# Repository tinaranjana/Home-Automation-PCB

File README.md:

# Home Automation PCB

A 4-layer smart home PCB designed in KiCad, built around the ESP32-WROOM-32. It controls 3 appliances (Light, AC and Exhaust) through opto-isolated relay channels.

## Features
- ESP32-WROOM-32 main controller
- 3 relay channels with PC817 optocoupler isolation
- NPN transistor driver and 1N4007 flyback diode on each channel
- LDR and DHT11 sensor headers, I2C LCD header
- 4 push-button inputs and a UART header
- 12 V DC input with 5 V (L7805) and 3.3 V (AMS1117) regulation

## Design Details
- Tool: KiCad 10
- 4 copper layers: F.Cu, In1.Cu, In2.Cu, B.Cu
- 209 pads, 67 nets, 44 vias, 0 unrouted
- Antenna keep-out zone for the ESP32

## Files
- `Home_Automation_PCB.pdf`: schematic, PCB layers, 3D views and BOM
- `ibom.html`: interactive BOM

## Status
Learning project. Feedback and suggestions are welcome!

## Author
Ranjana Yadav
linkedin.com/in/ranjana-yadav-ece

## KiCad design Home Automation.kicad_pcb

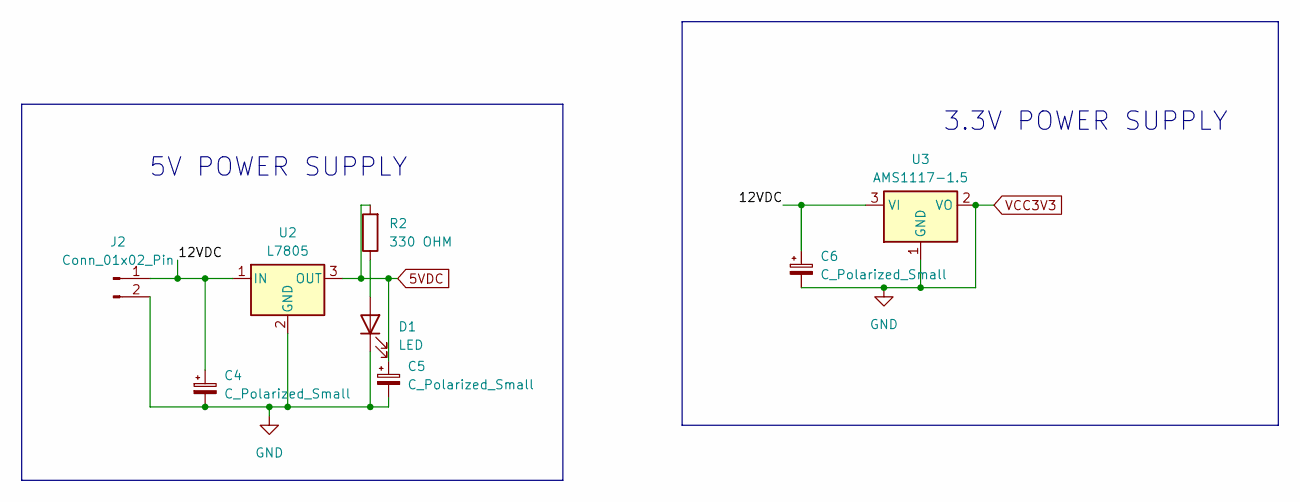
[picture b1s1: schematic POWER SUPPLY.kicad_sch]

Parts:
C4, C5, C6: C_Polarized_Small; CP_Elec_8x6.2
D1: LED; LED_D1.8mm_W3.3mm_H2.4mm
J2: Conn_01x02_Pin; TerminalBlock_Phoenix_MKDS-1,5-2_1x02_P5.00mm_Horizontal
R2: 330 OHM; R_0603_1608Metric
U2: L7805; TO-252-2
U3: AMS1117-1.5; SOT-223-3_TabPin2

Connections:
5VDC: C5.1, R2.2, U2.3 (OUT); also elsewhere on the board
/POWER SUPPLY/12VDC: C4.1, C6.1, J2.1, U2.1 (IN), U3.3 (VI)
GND: C4.2, C5.2, C6.2, D1.1 (K), J2.2, U2.2 (GND), U3.1 (GND), U3.2 (VO); also elsewhere on the board
unnamed: D1.2 (A), R2.1

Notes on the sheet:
5V POWER SUPPLY
3.3V POWER SUPPLY

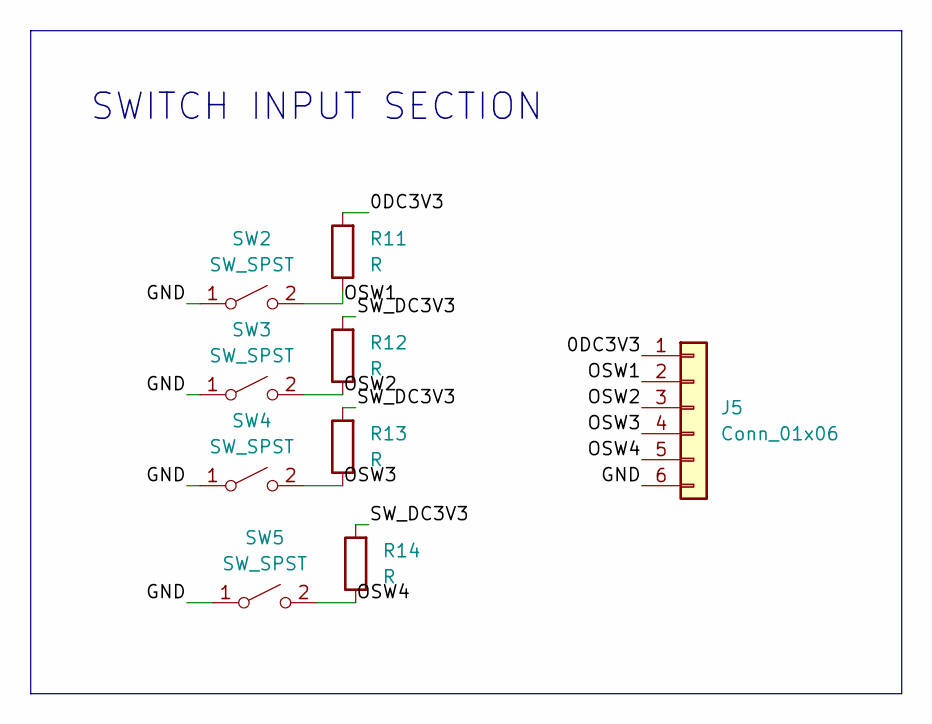
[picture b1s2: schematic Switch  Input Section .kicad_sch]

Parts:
J5: Conn_01x06; PinHeader_1x06_P2.54mm_Vertical_SMD_Pin1Left
R11, R12, R13, R14: R; R_0603_1608Metric
SW2, SW3, SW4, SW5: SW_SPST; SW_PUSH_6mm

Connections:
/Switch Input Section/0DC3V3: J5.1, R11.2
/Switch Input Section/GND: J5.6, SW2.1 (A), SW3.1 (A), SW4.1 (A), SW5.1 (A)
/Switch Input Section/OSW1: J5.2, R11.1, SW2.2 (B)
/Switch Input Section/OSW2: J5.3, R12.1, SW3.2 (B)
/Switch Input Section/OSW3: J5.4, R13.1, SW4.2 (B)
/Switch Input Section/OSW4: J5.5, R14.1, SW5.2 (B)
/Switch Input Section/SW_DC3V3: R12.2, R13.2, R14.2

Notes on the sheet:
SWITCH INPUT SECTION

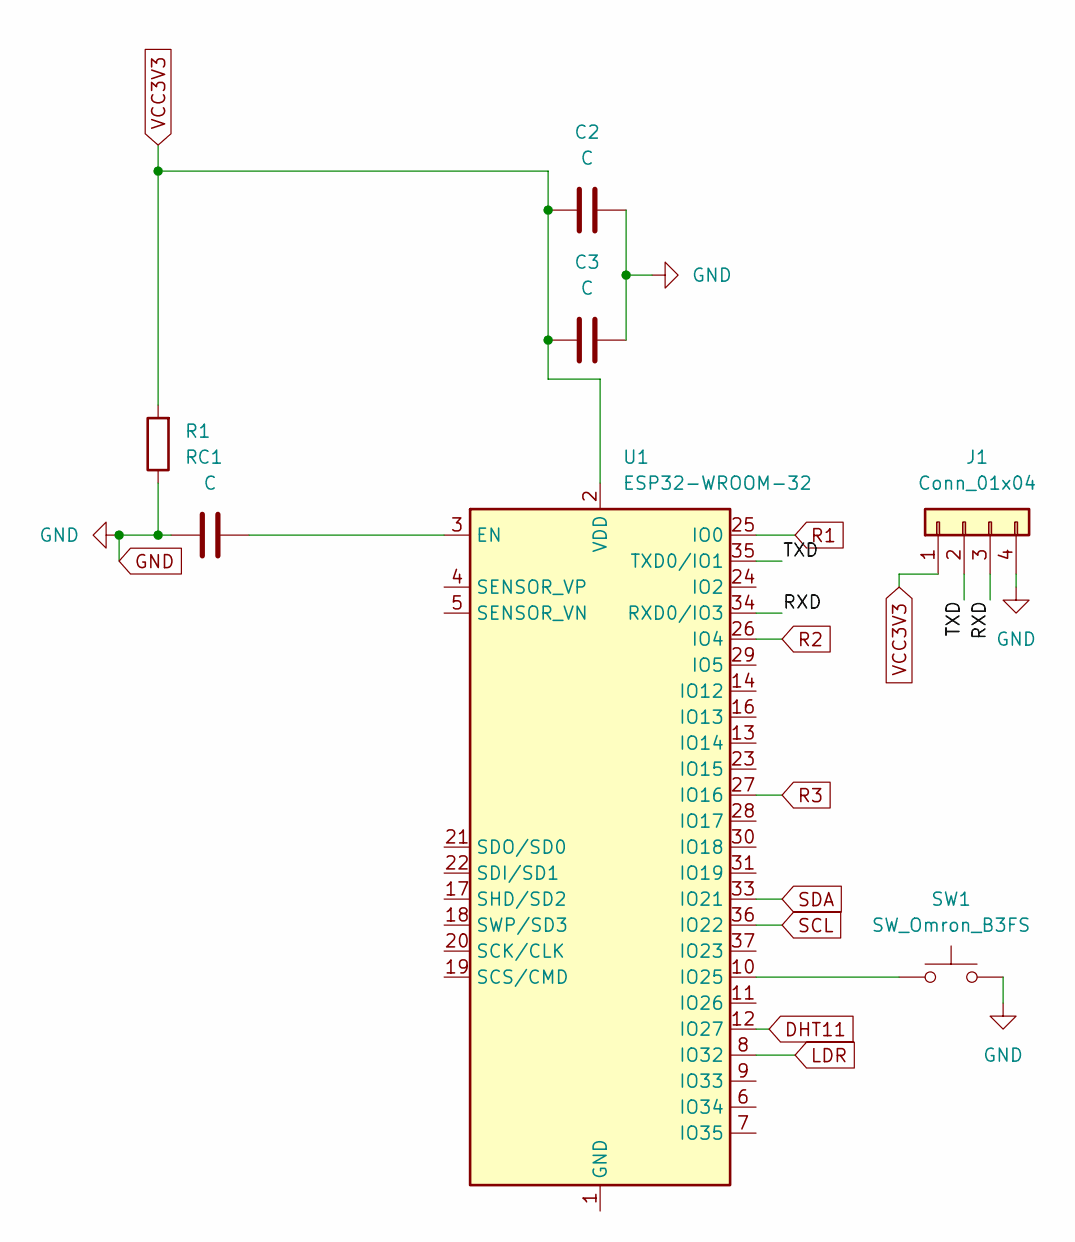
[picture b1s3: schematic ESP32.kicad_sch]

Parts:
C1, C2, C3: C; C_0201_0603Metric
J1: Conn_01x04; PinHeader_1x04_P2.54mm_Vertical_SMD_Pin1Left
R1: R; R_0603_1608Metric
SW1: SW_Omron_B3FS; SW_SPST_TS-1088-xR020
U1: ESP32-WROOM-32

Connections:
/ESP32/RXD: J1.3, U1.34 (RXD0/IO3)
/ESP32/TXD: J1.2, U1.35 (TXD0/IO1)
DHT11: U1.12 (IO27); also elsewhere on the board
GND: C1.1, C2.1, C2.2, C3.1, C3.2, J1.1, J1.4, R1.1, R1.2, SW1.2, U1.2 (VDD); also elsewhere on the board
LDR: U1.8 (IO32); also elsewhere on the board
unnamed: C1.2, U1.3 (EN)
unnamed: U1.1 (GND), U1.15 (GND), U1.38 (GND), U1.39 (GND)
unnamed: SW1.1, U1.10 (IO25)
R1: U1.25 (IO0); also elsewhere on the board
R2: U1.26 (IO4); also elsewhere on the board
R3: U1.27 (IO16); also elsewhere on the board
SCL: U1.36 (IO22); also elsewhere on the board
SDA: U1.33 (IO21); also elsewhere on the board

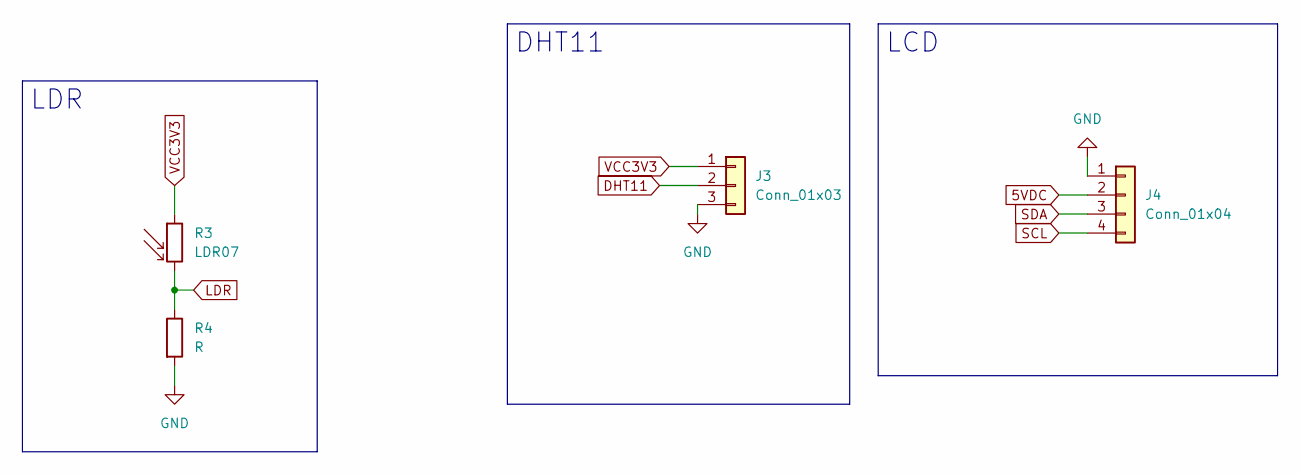
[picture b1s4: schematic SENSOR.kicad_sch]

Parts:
J3: Conn_01x03; PinHeader_1x03_P2.54mm_Vertical_SMD_Pin1Left
J4: Conn_01x04; PinHeader_1x04_P2.54mm_Vertical_SMD_Pin1Left
R3: LDR07; R_LDR_5.1x4.3mm_P3.4mm_Vertical
R4: R; R_0201_0603Metric

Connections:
5VDC: J4.2; also elsewhere on the board
DHT11: J3.2; also elsewhere on the board
GND: J3.1, J3.3, J4.1, R3.1, R4.2; also elsewhere on the board
LDR: R3.2, R4.1; also elsewhere on the board
SCL: J4.4; also elsewhere on the board
SDA: J4.3; also elsewhere on the board

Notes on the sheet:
LCD
DHT11
LDR

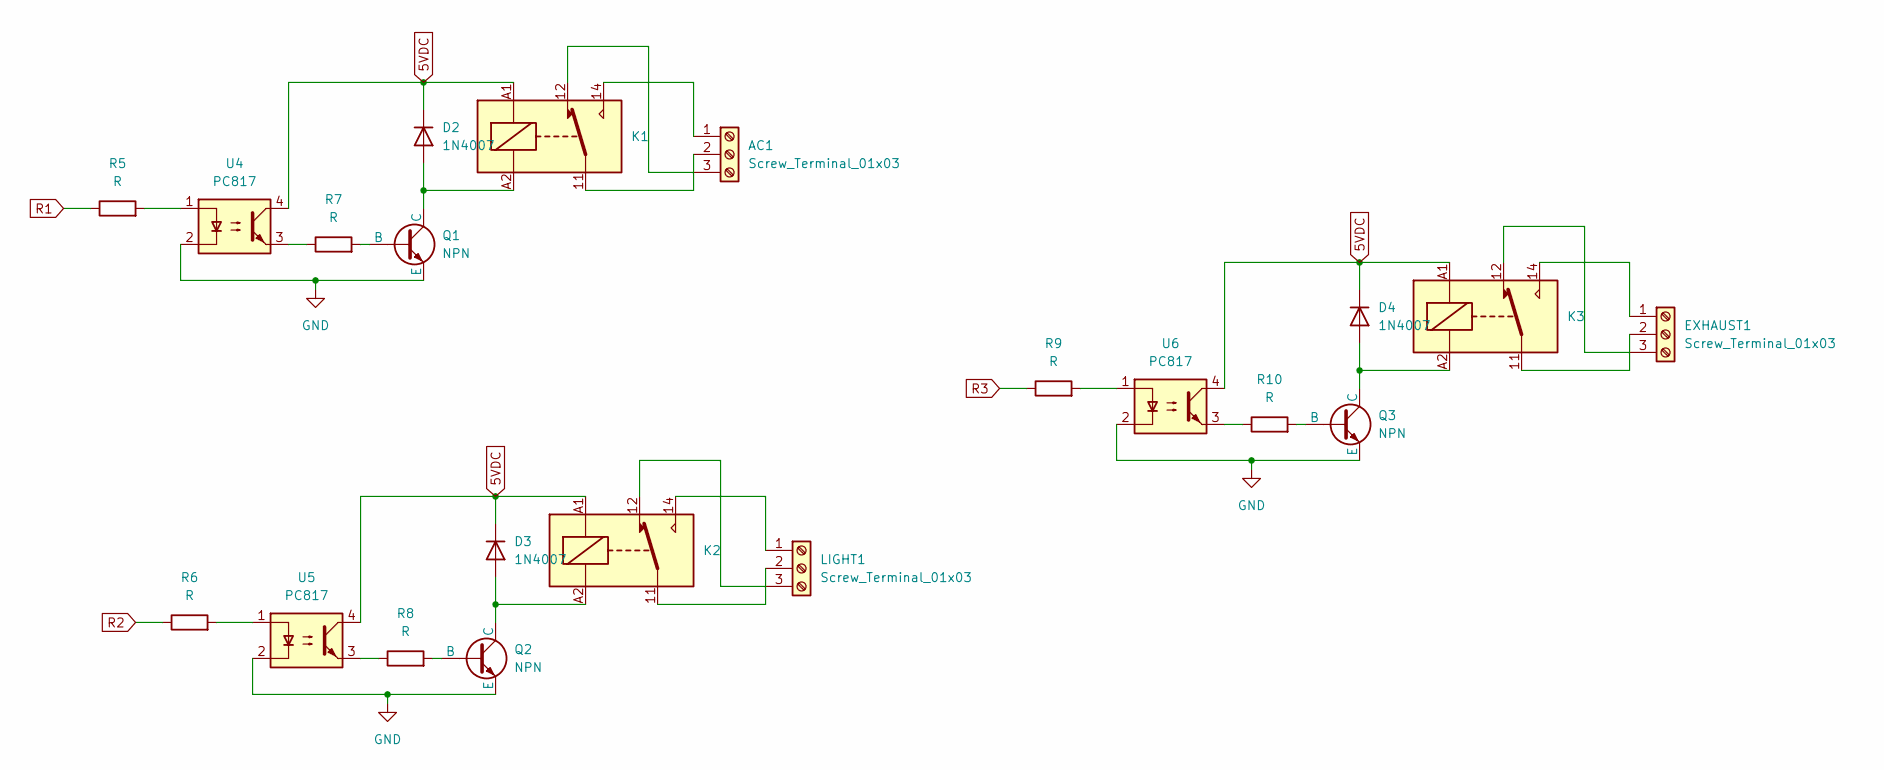
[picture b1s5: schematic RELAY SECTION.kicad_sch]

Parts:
AC1: Screw_Terminal_01x03; TerminalBlock_Phoenix_MKDS-1,5-3_1x03_P5.00mm_Horizontal
D2, D3, D4: 1N4007; D_0603_1608Metric
EXHAUST1: Screw_Terminal_01x03; TerminalBlock_Phoenix_MKDS-1,5-3_1x03_P5.00mm_Horizontal
K1, K2, K3: Fujitsu_FTR-LYCA005x; Relay_SPDT_Finder_36.11
LIGHT1: Screw_Terminal_01x03; TerminalBlock_Phoenix_MKDS-1,5-3_1x03_P5.00mm_Horizontal
Q1, Q2, Q3: NPN; SOT-23
R5, R6, R7, R8, R9, R10: R; R_0805_2012Metric_Pad1.20x1.40mm_HandSolder
U4, U5, U6: PC817; SO-4_4.4x4.3mm_P2.54mm

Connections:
5VDC: D2.1 (K), D3.1 (K), D4.1 (K), K1.A1, K2.A1, K3.A1, U4.4, U5.4, U6.4; also elsewhere on the board
GND: Q1.3 (E), Q2.3 (E), Q3.3 (E), U4.2, U5.2, U6.2; also elsewhere on the board
unnamed: AC1.1, K1.14
unnamed: AC1.2, K1.11
unnamed: AC1.3, K1.12
unnamed: D2.2 (A), K1.A2, Q1.1 (C)
unnamed: D3.2 (A), K2.A2, Q2.1 (C)
unnamed: D4.2 (A), K3.A2, Q3.1 (C)
unnamed: EXHAUST1.1, K3.14
unnamed: EXHAUST1.2, K3.11
unnamed: EXHAUST1.3, K3.12
unnamed: K2.14, LIGHT1.1
unnamed: K2.11, LIGHT1.2
unnamed: K2.12, LIGHT1.3
unnamed: Q1.2 (B), R7.2
unnamed: Q2.2 (B), R8.2
unnamed: Q3.2 (B), R10.2
unnamed: R5.2, U4.1
unnamed: R6.2, U5.1
unnamed: R7.1, U4.3
unnamed: R8.1, U5.3
unnamed: R9.2, U6.1
unnamed: R10.1, U6.3
R1: R5.1; also elsewhere on the board
R2: R6.1; also elsewhere on the board
R3: R9.1; also elsewhere on the board

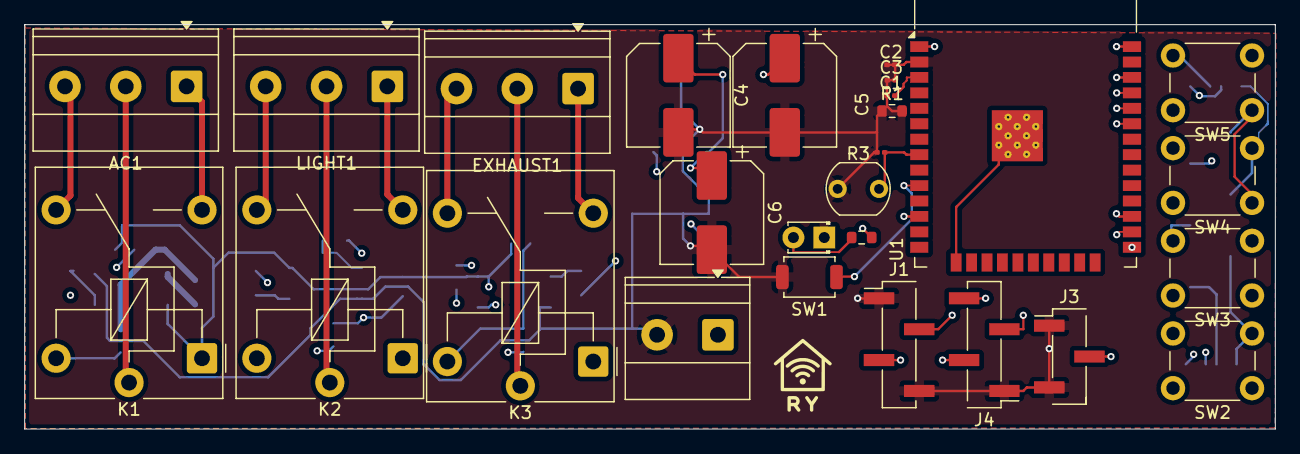
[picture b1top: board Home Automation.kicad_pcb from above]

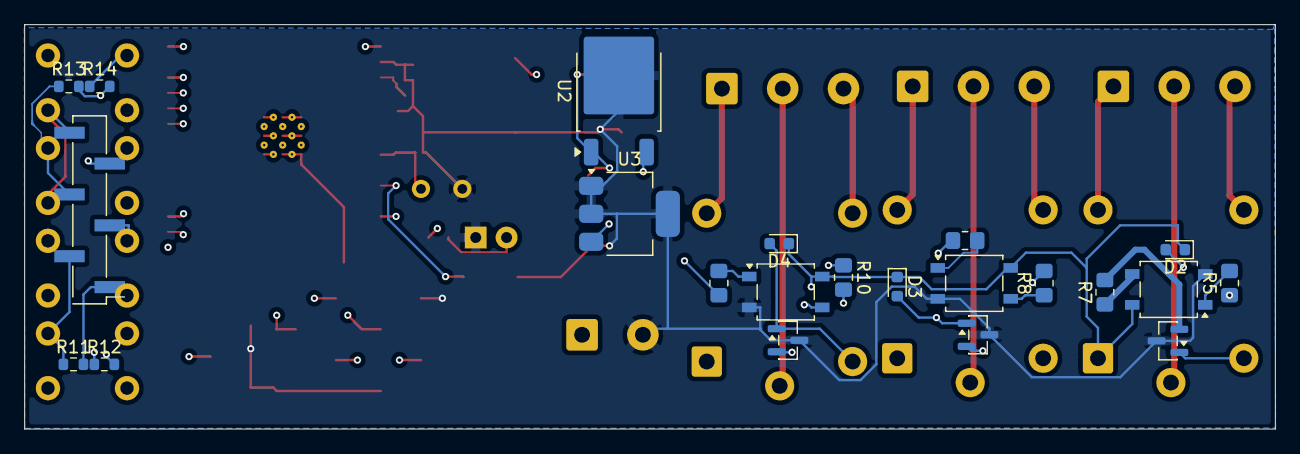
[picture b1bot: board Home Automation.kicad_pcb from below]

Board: 4 copper layers, 102.9 x 33.3 mm, 49 parts (22 on the bottom side), 44 nets.
